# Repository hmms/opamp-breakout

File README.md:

# opamp-breakout
opamp-breakout

simple differential opamp breakout board with an additional inverting opamp buffer amplifier with adjustable gain.

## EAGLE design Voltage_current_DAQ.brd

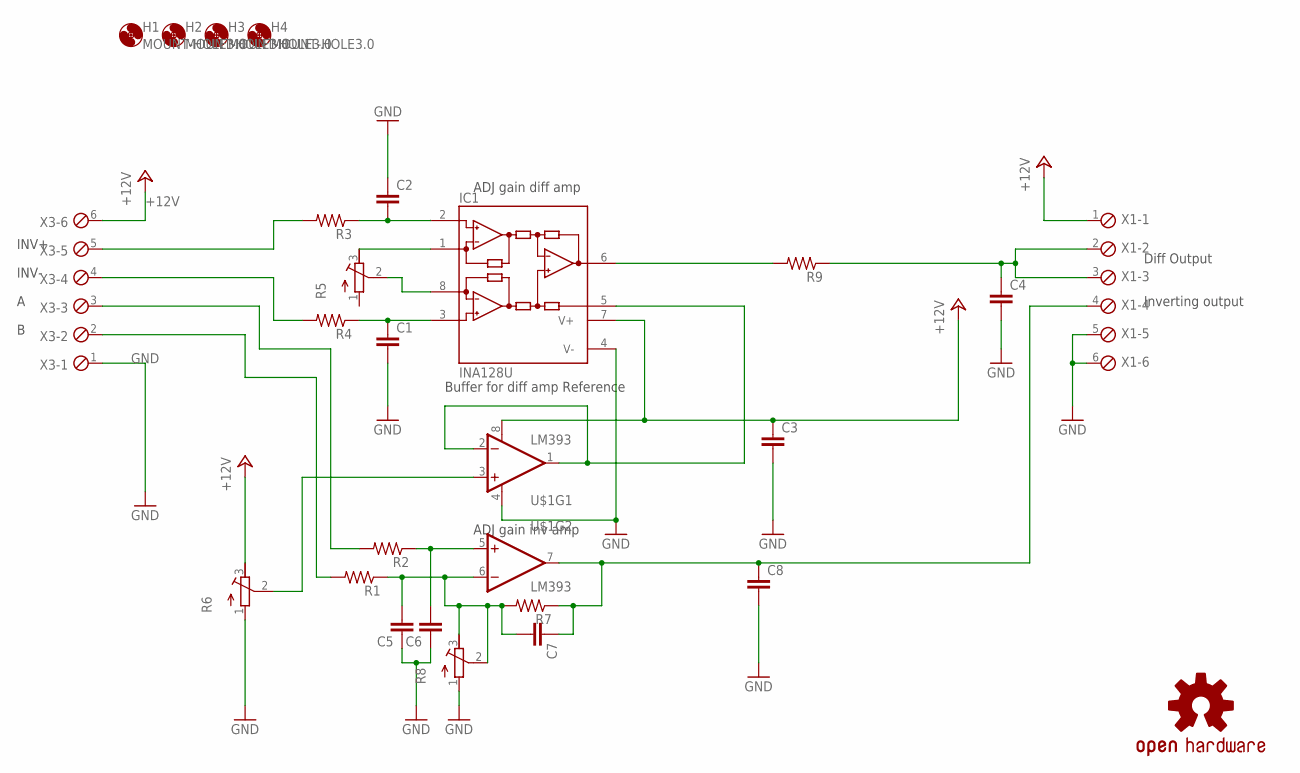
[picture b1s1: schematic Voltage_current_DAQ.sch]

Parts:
C1, C2, C3, C4, C5, C6, C7, C8: C-EUC0805; C0805
H1, H2, H3, H4: MOUNT-HOLE3.0; 3,0
IC1: INA128U; SO08
LOGO1: OSHW-LOGOL; OSHW-LOGO-L
R1, R3, R4, R7, R9: R-US_R0805; R0805
R2: R-US_R0603; R0603
R5, R6, R8: R-TRIMM64Y; RTRIM64Y
U$1: LM393; SO08
X1, X3: MPT6; 6POL254

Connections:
+12V: C3.1, IC1.7 (V+), U$1.8 (V+), X1.1, X3.6
+24V: R6.3 (E)
GND: C1.2, C2.1, C3.2, C4.2, C5.1, C6.1, C8.2, IC1.4 (V-), R6.1 (A), R8.1 (A), U$1.4 (V-), X1.5, X1.6, X3.1
unnamed: C2.2, IC1.2 (-IN), R3.1
unnamed: C1.1, IC1.3 (+IN), R4.1
unnamed: IC1.1 (RG), R5.3 (E)
unnamed: IC1.8 (RG), R5.2 (S)
unnamed: R3.2, X3.5
unnamed: IC1.6 (OUT), R9.2
unnamed: R4.2, X3.4
unnamed: C4.1, R9.1, X1.2, X1.3
unnamed: R6.2 (S), U$1.3 (+IN)
unnamed: IC1.5 (REF), U$1.1 (OUT), U$1.2 (-IN)
unnamed: C6.2, R2.1, U$1.5 (+IN)
unnamed: R1.2, X3.2
unnamed: C5.2, C7.2, R1.1, R7.2, R8.2 (S), R8.3 (E), U$1.6 (-IN)
unnamed: C7.1, C8.1, R7.1, U$1.7 (OUT), X1.4
unnamed: R2.2, X3.3

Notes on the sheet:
Diff Output
Inverting output
INV+
INV-
ADJ gain diff amp
ADJ gain inv amp
Buffer for diff amp Reference

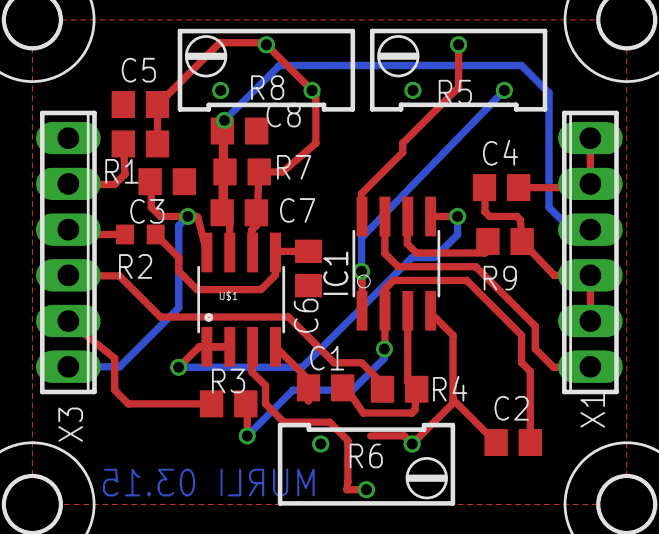
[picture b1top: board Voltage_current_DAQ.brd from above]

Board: 2 copper layers, 26 parts (1 on the bottom side), 17 nets.

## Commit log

2015-03-09 initial commit- added sch and brd files
2015-03-09 updated the initial layout
2015-03-16 gerbers generated sent to OSHpark

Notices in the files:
parts and their libraries:
SparkFun-AnalogIC: Licensing:Creative Commons ShareAlike 4.0 International - https://creativecommons.org/licenses/by-sa/4.0
